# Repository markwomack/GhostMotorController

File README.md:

# Ghost Motor Controller
<p>The Ghost Motor Controller is currently a proof-of-concept project that is creating motor controller hardware and software to manage two BLDC hoverboard/eScooter motors with 3-phase motor encoders. The goal is to use this motor controller as part of a mobile, differential drive robot, and to have a design that can eventually be reused with different underlying hardware and motors. The parameters of the project are to use as many 'off-the-shelf' parts as possible and as few custom designed parts. This is where the project name comes from: at the end of the day we are just putting a sheet over a collection of parts and calling it a motor controller. Custom PCBs are allowed since maintaining breadboards and/or protoboards in a robot can be cumbersome and require more room than desired or needed. However, much of the PCB design is (currently) integrating existing break out boards, mostly from Pololu and Sparkfun.</p>

## Status
<p>Ghost is currently in the 'proof-of-concept' phase. Most of the time thus far has been spent choosing the initial set of parts, getting a power system in place to support the parts, and designing the first version of circuitry that will make up the motor controller. The power system, motors, and a control circuit has been designed and tested. A custom PCB has been designed and will be integrated with the test system soon.</p>

## Hardware
Instead of creating a custom circuit to control the motors, an existing eScooter controller is being used. But since this controller doesn't have a programmatic interface, a microcontroller circuit is being designed. Basically a controller of a controller. This is the Ghost Motor Controller. The hardware will support I2C, 3 RC channel inputs, and a serial port for debugging output.

## Software
The Ghost Motor Controller will provide an API accessible through I2C. Using this API the user will be able to set/get configuration and set/get information and actions on the motors and associated encoders. Everything one needs to control the motors on a mobile, differential drive robot will be provided. It will be very similar to existing APIs for other popular controllers, like the RoboClaw.

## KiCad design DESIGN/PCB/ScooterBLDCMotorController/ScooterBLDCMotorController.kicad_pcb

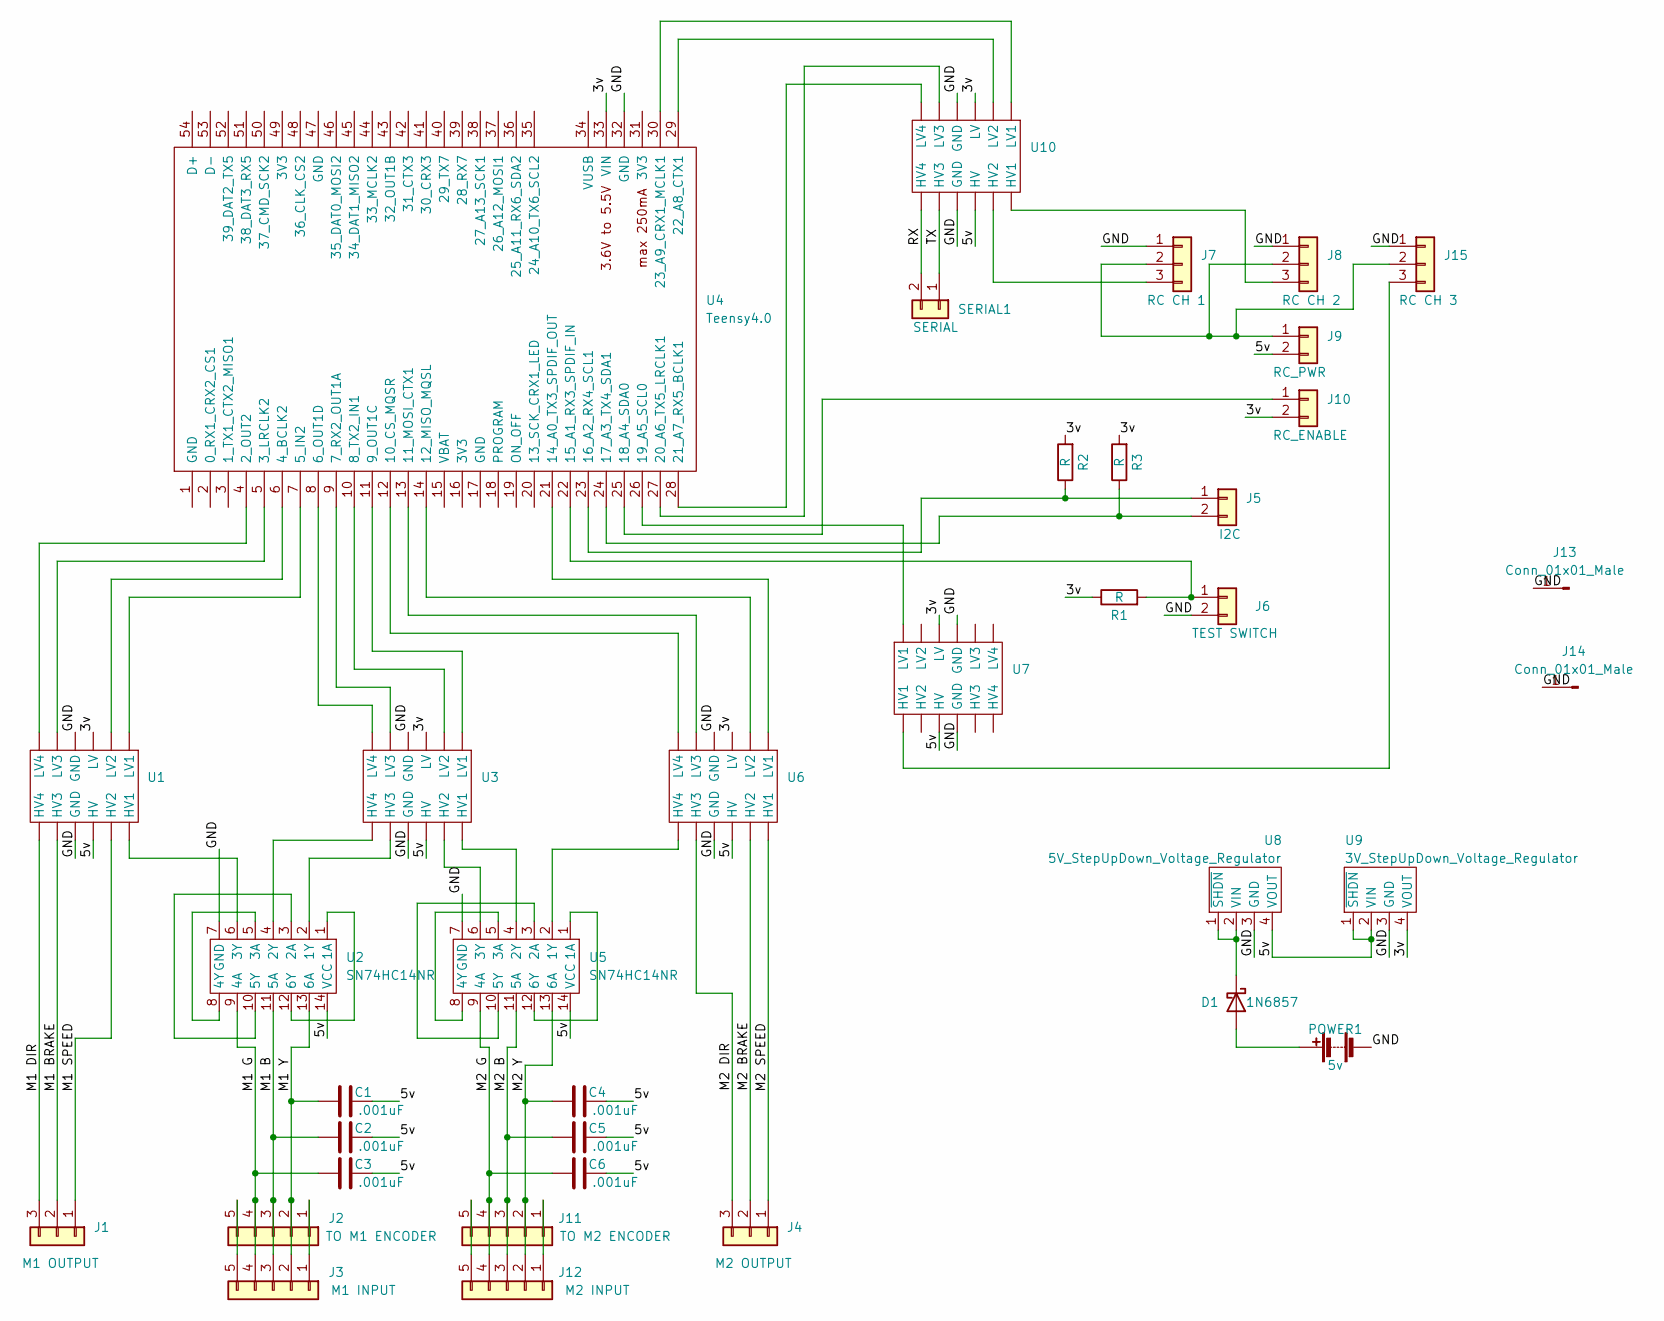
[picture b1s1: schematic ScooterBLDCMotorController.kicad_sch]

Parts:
C1, C2, C3, C4, C5, C6: .001uF; C_Axial_L3.8mm_D2.6mm_P7.50mm_Horizontal
D1: 1N6857; D_DO-35_SOD27_P7.62mm_Horizontal
J1: M1 OUTPUT; TerminalBlock_Altech_AK300-3_P5.00mm; LCSC C8393
J2: TO M1 ENCODER; JST_XH_B5B-XH-A_1x05_P2.50mm_Vertical; LCSC C157991
J3: M1 INPUT; TerminalBlock_Altech_AK300-5_P5.00mm; LCSC C395854
J4: M2 OUTPUT; TerminalBlock_Altech_AK300-3_P5.00mm; LCSC C8393
J5: I2C; JST_XH_B2B-XH-A_1x02_P2.50mm_Vertical; LCSC C158012
J6: TEST SWITCH; JST_XH_B2B-XH-A_1x02_P2.50mm_Vertical; LCSC C158012
J7: RC CH 1; JST_XH_B3B-XH-A_1x03_P2.50mm_Vertical; LCSC C161870
J8: RC CH 2; JST_XH_B3B-XH-A_1x03_P2.50mm_Vertical; LCSC C161870
J9: RC_PWR; PinHeader_1x02_P2.54mm_Vertical; LCSC C5116481
J10: RC_ENABLE; PinHeader_1x02_P2.54mm_Vertical; LCSC C5116481
J11: TO M2 ENCODER; JST_XH_B5B-XH-A_1x05_P2.50mm_Vertical; LCSC C157991
J12: M2 INPUT; TerminalBlock_Altech_AK300-5_P5.00mm; LCSC C395854
J13, J14: Conn_01x01_Male; PinHeader_1x01_P2.54mm_Vertical
J15: RC CH 3; JST_XH_B3B-XH-A_1x03_P2.50mm_Vertical; LCSC C161870
POWER1: 5v; JST_XH_B2B-XH-A_1x02_P2.50mm_Vertical; LCSC C158012
R1, R2, R3: R; R_Axial_DIN0204_L3.6mm_D1.6mm_P7.62mm_Horizontal
SERIAL1: SERIAL; JST_XH_B2B-XH-A_1x02_P2.50mm_Vertical; LCSC C158012
U1, U3, U6, U7, U10: Level Shifter
U2, U5: SN74HC14NR; DIP-14_W7.62mm; LCSC C2907
U4: Teensy4.0; Teensy40_sides
U8: 5V_StepUpDown_Voltage_Regulator; StepUpDown Voltage Regulator
U9: 3V_StepUpDown_Voltage_Regulator; StepUpDown Voltage Regulator

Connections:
/3v: J10.2, R1.1, R2.2, R3.2, U1.9 (LV), U3.9 (LV), U4.33 (VIN), U6.9 (LV), U7.9 (LV), U9.4 (VOUT), U10.9 (LV)
/5v: C1.2, C2.2, C3.2, C4.2, C5.1, C6.1, J9.2, U1.4 (HV), U2.14 (VCC), U3.4 (HV), U5.14 (VCC), U6.4 (HV), U7.4 (HV), U8.4 (VOUT), U9.1 (~SHDN), U9.2 (VIN), U10.4 (HV)
/GND: J6.2, J7.1, J8.1, J13.1, J14.1, J15.1, POWER1.2 (-), U1.3 (GND), U1.10 (GND), U2.7 (GND), U3.3 (GND), U3.10 (GND), U4.32 (GND), U5.7 (GND), U6.3 (GND), U6.10 (GND), U7.3 (GND), U7.10 (GND), U8.3 (GND), U9.3 (GND), U10.3 (GND), U10.10 (GND)
/M1 B: C2.1, J2.3, J3.3, U2.11 (5A)
/M1 BRAKE: J1.2, U1.2 (HV3)
/M1 DIR: J1.3, U1.1 (HV4)
/M1 G: C3.1, J2.4, J3.4, U2.9 (4A)
/M1 SPEED: J1.1, U1.5 (HV2)
/M1 Y: C1.1, J2.2, J3.2, U2.13 (6A)
/M2 B: C5.2, J11.3, J12.3, U5.11 (5A)
/M2 BRAKE: J4.2, U6.5 (HV2)
/M2 DIR: J4.3, U6.2 (HV3)
/M2 G: C6.2, J11.4, J12.4, U5.9 (4A)
/M2 SPEED: J4.1, U6.6 (HV1)
/M2 Y: C4.1, J11.2, J12.2, U5.13 (6A)
/RX: SERIAL1.2, U10.1 (HV4)
/TX: SERIAL1.1, U10.2 (HV3)
unnamed: D1.2 (A), POWER1.1 (+)
unnamed: D1.1 (K), U8.1 (~SHDN), U8.2 (VIN)
unnamed: J2.1, J3.1
unnamed: J2.5, J3.5
unnamed: J5.1, R2.1, U4.23 (16_A2_RX4_SCL1)
unnamed: J5.2, R3.1, U4.24 (17_A3_TX4_SDA1)
unnamed: J6.1, R1.2, U4.22 (15_A1_RX3_SPDIF_IN)
unnamed: J7.3, U10.5 (HV2)
unnamed: J8.3, U10.6 (HV1)
unnamed: J10.1, U4.25 (18_A4_SDA0)
unnamed: J11.1, J12.1
unnamed: J11.5, J12.5
unnamed: J7.2, J8.2, J9.1, J15.2
unnamed: J15.3, U7.6 (HV1)
unnamed: U1.6 (HV1), U2.6 (3Y)
unnamed: U1.7 (LV1), U4.7 (5_IN2)
unnamed: U1.8 (LV2), U4.6 (4_BCLK2)
unnamed: U1.11 (LV3), U4.5 (3_LRCLK2)
unnamed: U1.12 (LV4), U4.4 (2_OUT2)
unnamed: U2.1 (1A), U2.12 (6Y)
unnamed: U2.2 (1Y), U3.2 (HV3)
unnamed: U2.3 (2A), U2.10 (5Y)
unnamed: U2.4 (2Y), U3.1 (HV4)
unnamed: U2.5 (3A), U2.8 (4Y)
unnamed: U3.6 (HV1), U5.4 (2Y)
unnamed: U3.5 (HV2), U5.6 (3Y)
unnamed: U3.7 (LV1), U4.11 (9_OUT1C)
unnamed: U3.8 (LV2), U4.10 (8_TX2_IN1)
unnamed: U3.11 (LV3), U4.9 (7_RX2_OUT1A)
unnamed: U3.12 (LV4), U4.8 (6_OUT1D)
unnamed: U4.12 (10_CS_MQSR), U6.12 (LV4)
unnamed: U4.13 (11_MOSI_CTX1), U6.11 (LV3)
unnamed: U4.14 (12_MISO_MQSL), U6.8 (LV2)
unnamed: U4.21 (14_A0_TX3_SPDIF_OUT), U6.7 (LV1)
unnamed: U4.26 (19_A5_SCL0), U7.7 (LV1)
unnamed: U5.1 (1A), U5.12 (6Y)
unnamed: U5.2 (1Y), U6.1 (HV4)
unnamed: U5.3 (2A), U5.10 (5Y)
unnamed: U5.5 (3A), U5.8 (4Y)
unnamed: U4.30 (23_A9_CRX1_MCLK1), U10.7 (LV1)
unnamed: U4.29 (22_A8_CTX1), U10.8 (LV2)
unnamed: U4.27 (20_A6_TX5_LRCLK1), U10.11 (LV3)
unnamed: U4.28 (21_A7_RX5_BCLK1), U10.12 (LV4)

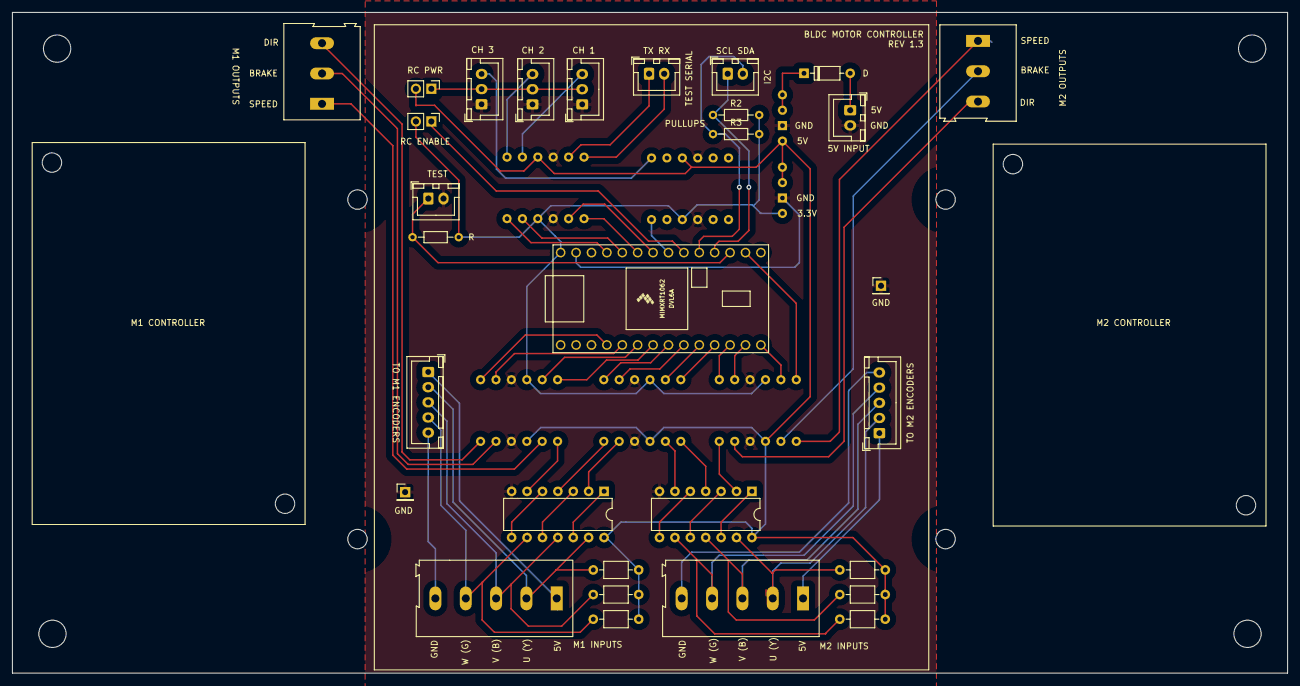
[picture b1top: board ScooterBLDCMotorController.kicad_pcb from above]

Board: 2 copper layers, 210.3 x 109.0 mm, 37 parts (0 on the bottom side), 60 nets.

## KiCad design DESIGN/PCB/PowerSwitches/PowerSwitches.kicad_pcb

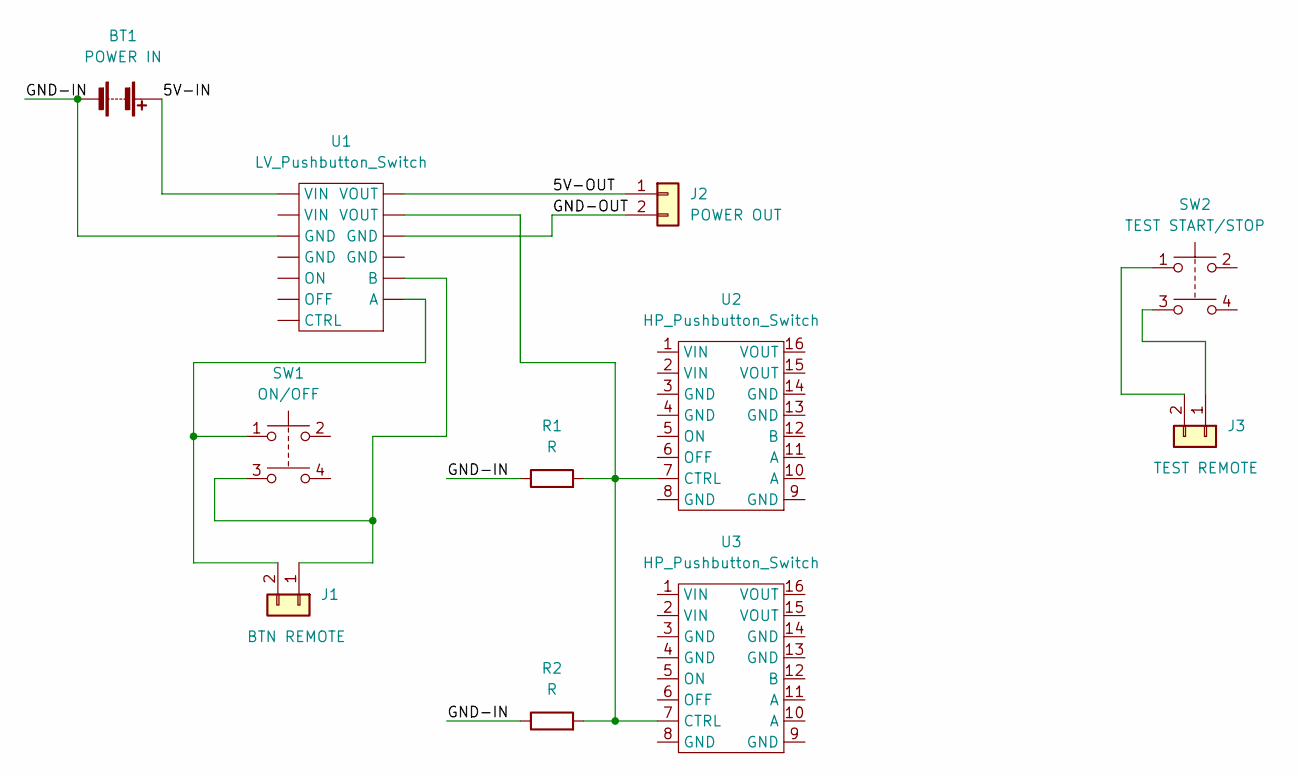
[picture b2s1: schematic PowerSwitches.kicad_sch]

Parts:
BT1: POWER IN; JST_XH_B2B-XH-A_1x02_P2.50mm_Vertical
J1: BTN REMOTE; JST_XH_B2B-XH-A_1x02_P2.50mm_Vertical
J2: POWER OUT; JST_XH_B2B-XH-A_1x02_P2.50mm_Vertical
J3: TEST REMOTE; JST_XH_B2B-XH-A_1x02_P2.50mm_Vertical
R1, R2: R; R_Axial_DIN0207_L6.3mm_D2.5mm_P7.62mm_Horizontal
SW1: ON/OFF; Small Dual Push Button
SW2: TEST START/STOP; Small Dual Push Button
U1: LV_Pushbutton_Switch; LV_PushButton_Switch
U2, U3: HP_Pushbutton_Switch; HV_PushButton_Switch

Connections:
/5V-IN: BT1.1 (+), U1.1 (VIN)
/5V-OUT: J2.1, U1.13 (VOUT)
/GND-IN: BT1.2 (-), R1.1, R2.1, U1.3 (GND)
/GND-OUT: J2.2, U1.11 (GND)
unnamed: J1.2, SW1.1, U1.8 (A)
unnamed: J3.2, SW2.1
unnamed: R1.2, R2.2, U1.12 (VOUT), U2.7 (CTRL), U3.7 (CTRL)
unnamed: J3.1, SW2.3
unnamed: J1.1, SW1.3, U1.9 (B)

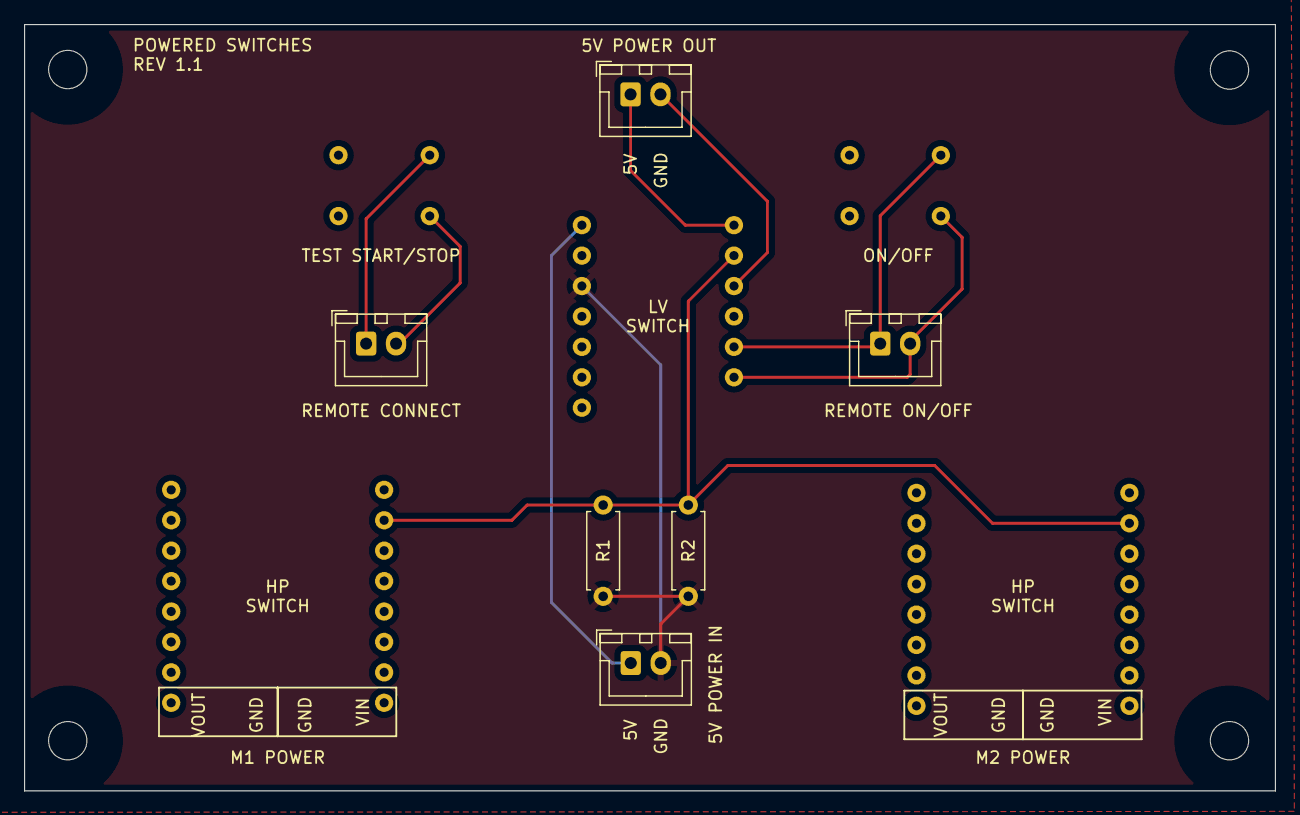
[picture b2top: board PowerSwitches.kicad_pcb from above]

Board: 2 copper layers, 104.4 x 64.0 mm, 11 parts (0 on the bottom side), 9 nets.

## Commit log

2022-03-24 Update OverallDesign.md
    Add References section.
2022-04-04 Uploading test example
2022-04-16 Added BLDCTest sketch
2023-01-01 Added com comments to match the board labeling.
2023-01-02 Used constant for button pin.
2023-01-02 Added spec images for BLDC controller
2023-01-02 Updated debug messages
    Previously commented out lines were changed to NOTIFICATION debug level.
2023-01-02 Switched pin assignments
    Switched pin assignments so that they work across all of the Teensy versions.
    Added some TODO comments.
2023-01-06 Updated and made slightly more efficient.
2023-01-07 Updated components
2023-01-07 Added fault counts instead of debug messages in the interrupts
2023-01-16 Updated battery switch listing
2023-01-31 Updated to latest motor design, upgraded to new task manager.
2023-02-01 Major cleanup, code for both motors to read encoders and run
2023-02-01 Update ProofOfConceptHardware.md
    Added miscellaneous section.
2023-02-01 More cleanup, debugging, and added license header
2023-02-02 Latest version from test machine
2023-02-04 changed pin assignments, added some test code
2023-02-05 Added more pins for RC, Serial, and I2C. KiCAD design.
2023-02-06 Latest PCB and Rev1.0 release
2023-02-06 Added sketch for controlling motors via RC input
2023-02-06 Updated pin assignments
2023-02-07 Implemented sketch to use RC channels to drive motors
2023-02-07 Working version of BLDCWithRCTest
2023-02-14 Rev 1.1 of power switch pcb.
2023-02-25 Fixed swapped connections on level shifter.
2023-03-05 Revision 1.2 of MotorController board
2023-03-17 Updated PCB to use terminals, added new DriveByRC code
2023-03-18 Compile fixes, debugging in process
2023-03-18 Updated to working version
2023-03-20 Code cleanup, RCTester
2023-03-20 minor changes
2023-03-21 Comment cleanups
2023-03-21 Comments and cleanup
2023-03-21 Removed obsolete code
2023-03-21 Added code to check for rc enable
2023-03-21 Small code adjustments
2023-03-21 Small adjustments
2023-03-21 Fixes to get back to working version
2023-03-21 Add option to run in single direction with no oscillation
2023-03-22 More adjustment
2023-03-27 Made PID control optional
2023-03-27 Speed adjustments
2023-03-30 Revision 1.3 for PCB
2023-03-31 Final rev1.3 changes
2023-04-30 DriveByRC updates and allow remote ota, ExternalConnection to manage WiFi
2023-04-30 Local changes to test ota
2023-05-01 OTA for ExternalConnection, UDP debug messages
2023-05-02 Clean up and changes to get UDP messages working better
2023-05-02 Changes for outgoing serial buffer
2023-05-03 Lots of changes to separate RC from speed control, and support MotorController vs MotorManager execution
2023-05-09 Latest versions
2023-05-09 .gitignore file
2023-05-11 Integrate CRCStream
2023-05-11 Integrated CRCStream into DriveByRC, added some named scripts
2023-05-20 Lots of cleanup
2023-05-20 More cleanup
2023-05-21 Upgrade to FlasherXUpdater usage
2023-05-21 Add update timeout and code to bleed off remaining update data
2023-05-22 Changes to get OTA updates to work correctly
2023-05-23 Working version for FlasherX updates and RampedPID
2023-07-24 Latest version of code
